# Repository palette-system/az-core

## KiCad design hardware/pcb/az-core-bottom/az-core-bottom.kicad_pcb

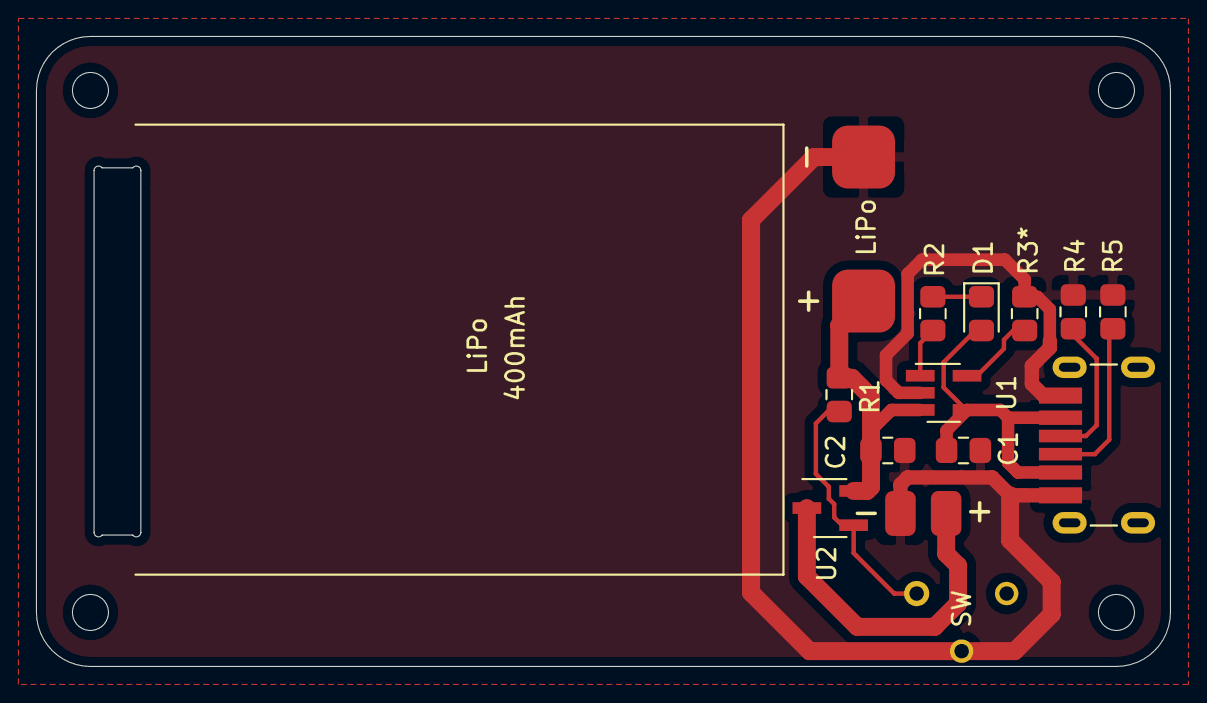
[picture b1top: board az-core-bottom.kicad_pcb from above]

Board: 2 copper layers, 63.0 x 35.0 mm, 14 parts (0 on the bottom side), 8 nets.

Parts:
C1, C2: 4.7μF; R_0805_2012Metric
D1: LED_RED; LED_0805_2012Metric
J3: vout; PinHeader_1x06_P2.54mm_Vertical
J4: Screw_Terminal_01x06; PinHeader_1x06_P2.54mm_Vertical
LiPo: lipo; Kailh-PG1425-X-Switch
LiPo#2: LiPo; JST_PH_S2B-PH-SM4-TB_1x02-1MP_P2.00mm_Horizontal
R1, R3*: 2.5kΩ; R_0805_2012Metric
R2, R4, R5: 1kΩ; R_0805_2012Metric
U1, U2: MCP73831-2-OT; SOT-23-5

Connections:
5V: J3.2, U2.2
GND: C1.2, C2.2, J3.1, J4.2, LiPo#2.2, R3*.1, R4.1, R5.1, U1.2
unnamed: C1.1, D1.2, U1.4
unnamed: D1.1, R2.2
unnamed: R2.1, U1.1
unnamed: R3*.2, U1.5
VIN: C2.1, LiPo#2.1, R1.1, U1.3, U2.5
VREAD: J4.1, R1.2, U2.4

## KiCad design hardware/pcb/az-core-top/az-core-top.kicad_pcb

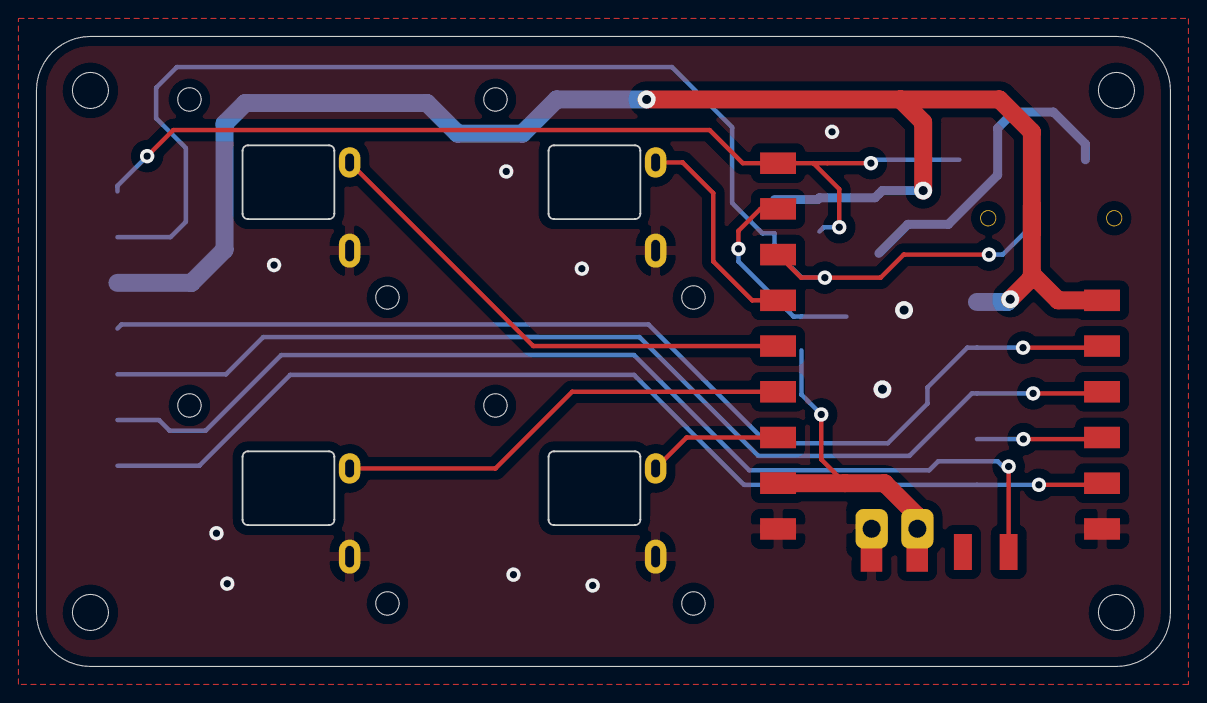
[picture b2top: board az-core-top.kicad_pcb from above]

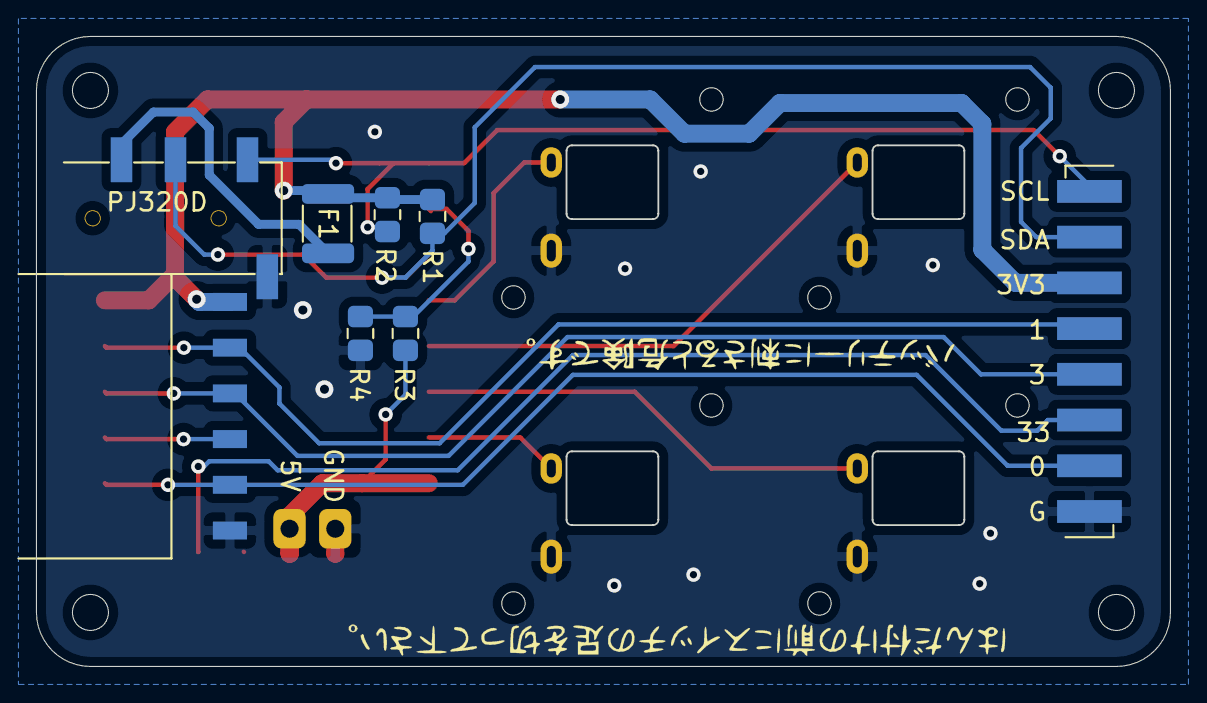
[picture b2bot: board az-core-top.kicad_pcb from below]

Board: 2 copper layers, 63.0 x 35.0 mm, 8 parts (6 on the bottom side), 7 nets.

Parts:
F1: 1kΩ; R_0805_2012Metric1.2
J3: Screw_Terminal_01x06; PinHeader_1x06_P2.54mm_Vertical
M5Stamp: Val**; StampPico_template
PJ320D: PJ320D_3.5mm_Jack
R1, R2, R3, R4: 1kΩ; R_0805_2012Metric

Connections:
5V: J3.2, M5Stamp.8, M5Stamp.11, R3.1
GND: J3.1, M5Stamp.9, M5Stamp.10, M5Stamp.14, PJ320D.4, R4.1
SCL: M5Stamp.1, PJ320D.1, R2.2
SDA: M5Stamp.3, PJ320D.2, R1.2
VCC: F1.2, M5Stamp.19, R1.1, R2.1
VIN: F1.1, PJ320D.3
VREAD: M5Stamp.2, R3.2, R4.2

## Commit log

2022-06-04 add firmware
2022-06-05 add aztool
2022-06-05 ioxp set
2022-06-05 define update
2022-06-11 add ap_list
2022-06-12 debug wifi ap
2022-06-14 add status rgb
2022-06-16 add diskinfo
2022-06-18 update eeprom
2022-06-19 update shift
2022-06-24 add power_read
2022-06-24 add analog_read
2022-06-29 update power read
2022-06-29 add aztool keyread
2022-06-30 update readkey
2022-06-30 add aztool mode
2022-07-05 update i2c
2022-07-05 update json
2022-07-16 add docs
2022-07-20 add esp-web-flasher
2022-07-20 update esptool
2022-07-20 add bin
2022-07-21 add tester
2022-07-22 add sample
2022-07-29 add sleep
2022-07-30 update text
2022-07-30 add hardware
2022-08-01 add message
2022-08-04 ver 0.1.3
2022-08-04 add erase
2022-08-04 mesg update
2022-08-09 add i2c_ioxp
2022-08-10 add i2c rotaly
2022-08-11 ver 1.0.4
2022-08-13 add rotary callback
2022-08-13 update opt
2022-08-14 pin 32 bug
2022-08-16 option bug
2022-08-25 add pim447
2022-08-29 add black tester
2022-08-30 add black zip
2022-08-30 add import doc
2022-09-09 add ver 0.1.7
2022-09-09 add mouse scroll
2022-09-09 update scroll
2022-09-11 add img
2022-09-11 add tool img
2022-09-19 update zip
2022-10-15 add power_saving_mode and az1uball_mode
2022-10-15 add change mode
2022-10-17 add firmware status
2022-11-06 add flick
2022-11-11 pim update
2022-12-17 esp32s3
2022-12-20 hid raw func
2022-12-21 update hid raw
2022-12-27 add esp32s3
2022-12-28 update define
2023-06-17 add hold setting
2023-06-18 set delay
2023-06-29 file clean
2023-06-30 bug edit
2023-07-01 add hid pin set
2023-07-07 add doc
2023-07-08 add i2c callback
2023-07-17 add az-expander
2023-07-22 add 1.17 bin
2023-07-22 add esportho zip
2023-07-22 update esportho zip
2023-07-26 update esp32 s3 build
2023-07-26 update s3 bin
2023-07-26 bin rename
2023-07-26 update config
2023-07-30 add oled
2023-08-21 add hall switch
2023-09-17 update file_all_remove
2023-09-17 add hall range
2023-09-17 add get_keymap_one
2023-09-18 add sub_press
2023-10-01 update black firm
2023-11-01 add nubkey
2024-03-01 nubkey update
2024-05-02 add magicpad
2024-11-13 ioエキスパンダのリセット動作
2024-11-14 lib_update
2024-11-15 add serial
2024-11-19 add serial input
2024-11-23 add myserial
2024-12-06 add logic flag
2024-12-17 add ir setting
2024-12-18 add irsetting
2024-12-20 update restart wdt
2024-12-31 add azsensor
2024-12-31 link update
2024-12-31 update doc
2024-12-31 doc update
2025-01-02 update restart
2025-01-02 add source link
2025-01-03 update azir command
2025-01-04 add setting png
2025-01-04 update bin
2025-02-13 add esp32 c6 nomal ble
2025-02-21 add c6 option
2025-02-22 add wifi flag
2025-03-10 update status_pin
2025-03-14 add power
2025-03-14 add azcard
2025-03-14 add link
2025-03-18 add check firm
2025-03-19 add azpocket
2025-03-19 update pocket firm
2025-03-19 update link
2025-03-19 add log
2025-03-19 update proto
2025-03-19 add import
2025-03-19 test esptool connect
2025-03-19 add esploader
2025-03-19 esptool
2025-03-19 esptool test
2025-03-19 tool test
2025-03-20 test
2025-03-20 tool
2025-03-20 update c6 firm
2025-03-21 add clear button
2025-04-23 add zip
2025-04-30 move import.zip
2025-04-30 add test firm
